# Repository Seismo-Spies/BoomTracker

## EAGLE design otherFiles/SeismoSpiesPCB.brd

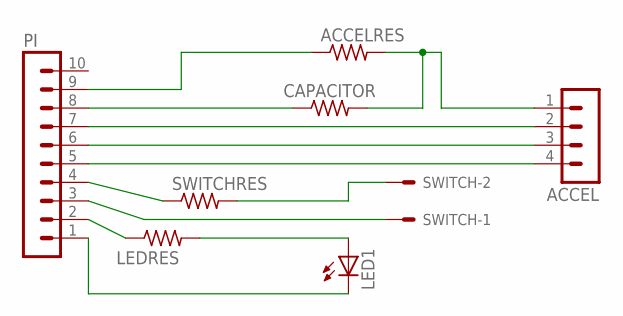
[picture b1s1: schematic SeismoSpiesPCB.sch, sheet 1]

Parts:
ACCEL: 04_PIN-HEADER; MA04-1
ACCELRES: 4.7 K; RESISTOR
CAPACITOR: RESISTOR0204/7; RESISTOR
LED1: LED3MM
LEDRES: RESISTOR0204/7; RESISTOR
PI: 10_PIN-HEADER-(FROM_ARDUINO); MA10-1
SWITCH: 02_PIN-HEADER; 02_PIN
SWITCHRES: RESISTOR0204/7; RESISTOR

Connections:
unnamed: ACCEL.4, PI.5
unnamed: PI.4, SWITCHRES.1
unnamed: SWITCH.2, SWITCHRES.2
unnamed: PI.3, SWITCH.1
unnamed: LEDRES.1, PI.2
unnamed: ACCEL.1, ACCELRES.2, CAPACITOR.2
unnamed: ACCEL.3, PI.6
unnamed: ACCELRES.1, PI.9
unnamed: CAPACITOR.1, PI.8
unnamed: ACCEL.2, PI.7
unnamed: LED1.A, LEDRES.2
unnamed: LED1.K (C), PI.1

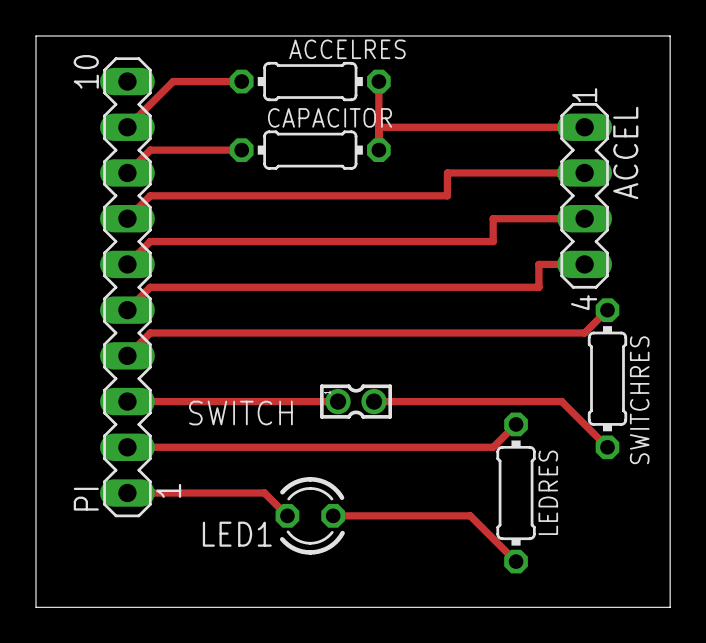
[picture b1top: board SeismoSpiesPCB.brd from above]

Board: 2 copper layers, 35.2 x 31.7 mm, 8 parts (0 on the bottom side), 12 nets.
